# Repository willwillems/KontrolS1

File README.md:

The following info is all about the S4 MK1, the MK2 has a different (non-panelized) PCB design and thus doesn't allow for reusing the original PCB's without serious modifications. The MK3 also has a single PCB for the mixer and deck sections.

## Setup
- Use the `Kontrol_S1_LC_OLED` sketch
- Either `#include "unit_d.h"` or `#include "unit_c.h"` based on the unit
- Uncomment `#define SCREEN` if using the OLED module
- Edit the `MIDI_NAME` in the `name.c` file to the desired name (these cannot conflict with other S1 units you're using)
- Flash the firmware

## Led off states
All leds are controlled by a transistor activated by the 595 chip. However not all are connected the same way, sending 6 all-off byte packages (`0b00000000`) will turn some of the LED's on, these specific bits to be set to HIGH instead of LOW in order to be turned off.

```
// LED OFF STATES from least significant bit (so notation is in reverse)
// -- BYTE [0]: 0b01010101 --
// CUE1 green - CUE1 blue - CUE2 green - CUE2 blue - CUE3 green - CUE3 blue - CUE4 green - CUE4 blue 
// -- BYTE [1]: 0b00000000 --
// Sample 1 - Sample 2 - Sample 3 - Sample 4 - SYNC - CUE - PLAY - SHIFT
// -- BYTE [2]: 0b11000000 --
// ON AIR - SAMPLES - DECK A/B - DECK C/D - KEYLOCK - MASTER - TEMPO OFFSET UP - TEMPO OFFSET DOWN
// -- BYTE [3]: 0b00000000 --
// LOOP IN - LOOP OUT - TOGGLE DECK C/D - LOAD - NONE - NONE - NONE -NONE
// -- BYTE [4]: 0b11111111 -- LEFT DIGIT
// UP-MIDDLE - UP-RIGHT - DOT - UP-LEFT - DOWN-LEFT - DOWN-MIDDLE - MIDDLE-MIDDLE - DOWN-RIGHT
// -- BYTE [5]: 0b11111111 -- RIGHT DIGIT
// DM - DL - UL - UM - UR - DR - MM - DOT
```

## Button off states
The first four bits of the last packet are connected to GND trough some 330 R resistors. 

```
// BUTTON OFF STATES
// -- BYTE [0]: 0B00000000 --
// PLAY - CP4 - CUE - CP3 - SYNC - CP2 - SHIFT - CP1
// -- BYTE [1]: 0B00000000 --
// S4 - LOAD - S3 - LOOP OUT - S2 - LOOP IN - DECK C/D
// -- BYTE [2]: 0B00001100 --
// X - X - X - X - ENC-R BUT - ENC-L BUT - OFFSET DOWN - OFFSET UP
```

## Pinout
This is the pinout for the DECK A board the DECK B connector is almost identical (but mirrored). The two exceptions are pin 2 and 13, ~~I have no idea what pin 2 is~~ pin 2 is the 165's DS on the DECK B unit. Click [here](https://i.imgur.com/EdCKgI3.jpg) for the DECK B section.

> WARNING: Pinout changed, check below.

```
// 595’s output enable is connected to GND.
// 165’s CE (chip enable) is connected to GND.
// (13, 14, 15), (16, 17) and (18, 19) are connected together.

1. Q7 (serial out 165)
2. GND (DS from 165's on DECK B)
3. PL (latch pin 165)
4. CP (clock input 165)
5. ENC4-R (330 R)
6. ENC5-L (330 R)
7. ENC4-R (330 R)
8. ENC5-L (330 R)
9. Q7S (serial out 595) (for DECK B this is the serial out of the 4 upper 595's)
10. DS (serial in 595) (for DECK B this is the serial in of the 2 lower 595's)

11. ST_CP (latch pin 595)
12. SH_CP (clock input 595)
13. GND (For DECK B this is the serial in for the 4 upper 595's)
14. GND
15. GND
16. LED V1 (5v but can just be 3.v)
17. LED V1 (5v but can just be 3.v)
18. LED V2 (3.3v)
19. LED V2 (3.3v)
20. VCC

1. GND
2. VCC
3. POT
4. GND
```

## Chip connections

### 74HC595

There are 6 595 chips chained together (the serial out(`Q7S`) for the last 595 is exposed as pin 9 on the connector).

- `ST_CP` and `SH_CP` of every chip are connected to connector pin 11 and 12.
- `MR` is connected to `VCC` on every chip.
- Output enable (`OE`) is connected to `GND` on every chip.

### 74HC165

There are 3 165 chips chained together.

- Clock enable(`CE`) is connect to `GND` on every chip.
- `PL` and `CP` of every chip are connected to connector pin 3 and 4.

## Jog wheels

The rotation of the jogs is measured by two photo-interrupters ([KTIR0611S](http://www.farnell.com/datasheets/2307823.pdf)). The "push down" of the jog is measured by a photo sensor that gets blocked when you push the platter down on it.

### Connections
The 6 pin JST connector is connected to the circuit with the two photo-interrupters. There is also a connection to a third photo-interrupter but they did not end up mounting and integrating this third one into the final product.
```
1. VCC (3.3v)
2. VCC (3.3v) (this "enables" the optical readings?) 
3. GND
4. ENC R
5. ENC L
6. ENC M (not connected or mounted)
```
The 3 color push cable coming out of the jog:
```
BLUE. GND
RED. VCC (3.3V)
WHITE. SIGNAL (analog read: 800~900 off, 1023 on)
-. DUMMY (unused pin on 4-pin JST connector) 
```
> ## Warning
> The jog press is not yet working so the info about it is possibly wrong. The MK1 does seem to use a IR proximity sensor (probably the [HSDL-9100-024](https://docs.broadcom.com/doc/AV02-2259EN) but so far no reliable readings have been produced. The MK2 uses an Ambient Light Sensor with an I2C Interface called the [VNCL4000](https://cdn-shop.adafruit.com/datasheets/vcnl4000.pdf). The current MK1 problems might just be calibration issues but could also be something more serious.

## Observations
- VCC should be 3.3v, not 5v. The 595 works with 5v and you will not fry the LED's but the 165 will not work and you might damage it.
- You can easily run the 165 and 595 chips with hardware SPI.
- The left and right circuit board are not identical at all though the connectors appear to be.

## Custom FX PCB

The custom FX PCB has the same layout on both sides so only one version is required (it has both the L&R mounting holes). The custom FX PCB provides a 165 and 595 interface for the buttons and LED's respectively and a separate connector for the potentiometer signals.

### Pinout

```
1. INH (165-15) [Clock enable]
2. SER (165-10) [Serial data input]
3. QH (595-9) [Serial data output]
4. LATCH 165 (165-1) [Parallel load input]
5. RCK (595-12) [storage register clock input]
6. QH (165-9) [Serial out]
7. SER (595-14)[Serial data input]
8. CLOCK
9. GND
10. VCC

11. VCC
12. GND
13. FX_3
14. FX_2
15. FX_1
16. FX_DW
```

## Parts

These simplified BOM's are for the MK4 releases of the brain and pot boards.

### Brain board

These are the parts needed to populate 1 brain board, to convert one S4 to two S1 units you'd need these parts x2.

| Part                                   | Amount | Value |
| -------------------------------------- | ------ | ----- |
| Molex Picoblade (1.25mm) 10-pin        | 3      |       |
| Molex Picoblade (1.25mm) 8-pin         | 1      |       |
| Molex Picoblade (1.25mm) 6-pin         | 3      |       |
| Molex Picoblade (1.25mm) 4-pin         | 2      |       |
| M3 metal standoffs                     | 4      | 15mm  |
| M3 metal screws                        | 8      | 6mm   |
| USB-B socket                           | 1      |       |
| Teensy LC                              | 1      |       |
| Capacitor US 1206                      | 1      | 100nF |
| Resistor US 1206 (0805 compatible)     | 1      | 1M    |

The 1M resistor might need a higher value.

### Pot board

These are the parts needed to populate 1 brain board, to convert one S4 to two S1 units you'd need these parts x2. The standoffs needed are already included with the brain BOM.

| Part                                   | Amount | Value |
| -------------------------------------- | ------ | ----- |
| Molex Picoblade (1.25mm) 10-pin        | 1      |       |
| Molex Picoblade (1.25mm) 6-pin         | 1      |       |
| Resistor US 0805                       | 5      | 82    |
| Resistor US 0805                       | 8      | 10K   |
| 74HC595D                               | 1      |       |
| 74HC165D                               | 1      |       |
| Capacitor US 1206                      | 6      | 100nF |

The four capacitors for the potentiometers might need a lower value.

## Custom OLED PCB

Contains adapter from 1.25mm JST to OLED, a step-up to 12V and some passive components the OLED driver needs.

### Pinout

```
1. GND
2. CLOCK
3. GND
4. MOSI
5. SS-SCREEN
6. VCC
7. DC
8. RST
```

# Screen

The screen uses https://github.com/ErikMinekus/traktor-api-client to get data from traktor + a local server to send it to the teensy over serial.

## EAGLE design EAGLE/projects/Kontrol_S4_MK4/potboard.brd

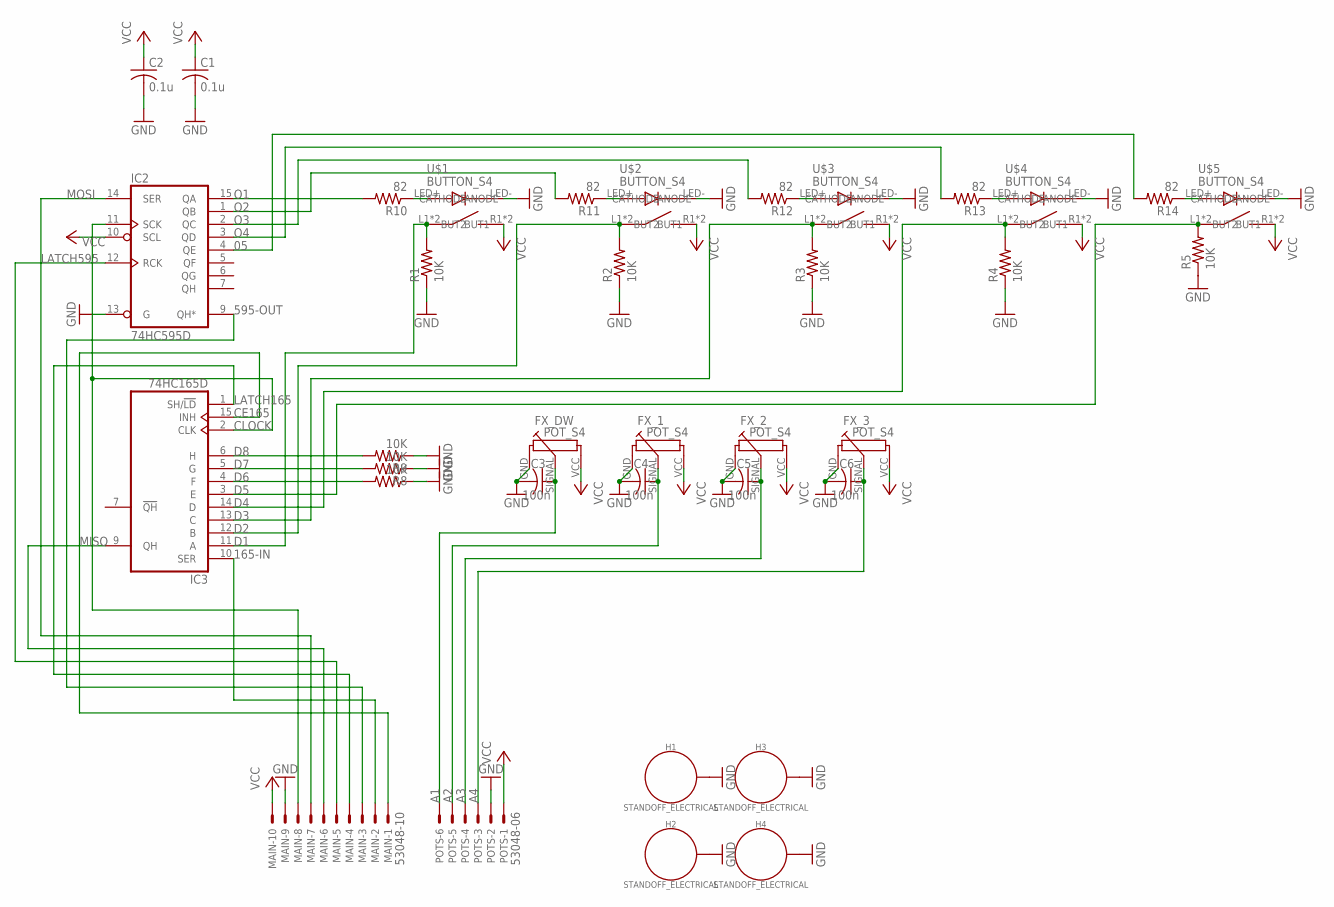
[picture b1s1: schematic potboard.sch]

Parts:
C1, C2: 0.1u; C1206
C3, C4, C5, C6: 100n; C1206
FX_1, FX_2, FX_3: POT_S4
FX_DW: POT_S4
H1, H2, H3, H4: STANDOFF_ELECTRICAL; STANDOFF-ELECTRICAL
IC2: 74HC595D; SO16
IC3: 74HC165D; SO16
MAIN: 53048-10
POTS: 53048-06
R1, R2, R3, R4, R5, R6, R8, R9: 10K; R0805
R10, R11, R12, R13, R14: 82; R0805
U$1, U$2, U$3, U$4, U$5: BUTTON_S4

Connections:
05: IC2.4 (QE), R14.2
165-IN: IC3.10 (SER), MAIN.2
595-OUT: IC2.9 (QH*), MAIN.3
A1: C3.1, FX_DW.SIGNAL (1S), POTS.6
A2: C4.1, FX_1.SIGNAL (1S), POTS.5
A3: C5.1, FX_2.SIGNAL (1S), POTS.4
A4: C6.1, FX_3.SIGNAL (1S), POTS.3
CE165: IC3.15 (INH), MAIN.1
CLOCK: IC2.11 (SCK), IC3.2 (CLK), MAIN.8
D1: IC3.11 (A), R1.2, U$1.L1 (BUT1), U$1.L2 (BUT1)
D2: IC3.12 (B), R2.2, U$2.L1 (BUT1), U$2.L2 (BUT1)
D3: IC3.13 (C), R3.2, U$3.L1 (BUT1), U$3.L2 (BUT1)
D4: IC3.14 (D), R4.2, U$4.L1 (BUT1), U$4.L2 (BUT1)
D5: IC3.3 (E), R5.2, U$5.L1 (BUT1), U$5.L2 (BUT1)
D6: IC3.4 (F), R6.2
D7: IC3.5 (G), R8.2
D8: IC3.6 (H), R9.2
GND: C1.2, C2.2, C3.2, C4.2, C5.2, C6.2, FX_1.GND (1A), FX_2.GND (1A), FX_3.GND (1A), FX_DW.GND (1A), H1.P1, H2.P1, H3.P1, H4.P1, IC2.8 (GND), IC2.13 (G), IC3.8 (GND), MAIN.9, POTS.2, R1.1, R2.1, R3.1, R4.1, R5.1, R6.1, R8.1, R9.1, U$1.LED- (CATHODE), U$2.LED- (CATHODE), U$3.LED- (CATHODE), U$4.LED- (CATHODE), U$5.LED- (CATHODE)
LATCH165: IC3.1 (SH/!LD), MAIN.4
LATCH595: IC2.12 (RCK), MAIN.5
MISO: IC3.9 (QH), MAIN.6
MOSI: IC2.14 (SER), MAIN.7
unnamed: R10.1, U$1.LED+ (ANODE)
unnamed: R11.1, U$2.LED+ (ANODE)
unnamed: R12.1, U$3.LED+ (ANODE)
unnamed: R13.1, U$4.LED+ (ANODE)
unnamed: R14.1, U$5.LED+ (ANODE)
O1: IC2.15 (QA), R10.2
O2: IC2.1 (QB), R11.2
O3: IC2.2 (QC), R12.2
O4: IC2.3 (QD), R13.2
VCC: C1.1, C2.1, FX_1.VCC (1E), FX_2.VCC (1E), FX_3.VCC (1E), FX_DW.VCC (1E), IC2.10 (SCL), IC2.16 (VCC), IC3.16 (VCC), MAIN.10, POTS.1, U$1.R1 (BUT2), U$1.R2 (BUT2), U$2.R1 (BUT2), U$2.R2 (BUT2), U$3.R1 (BUT2), U$3.R2 (BUT2), U$4.R1 (BUT2), U$4.R2 (BUT2), U$5.R1 (BUT2), U$5.R2 (BUT2)

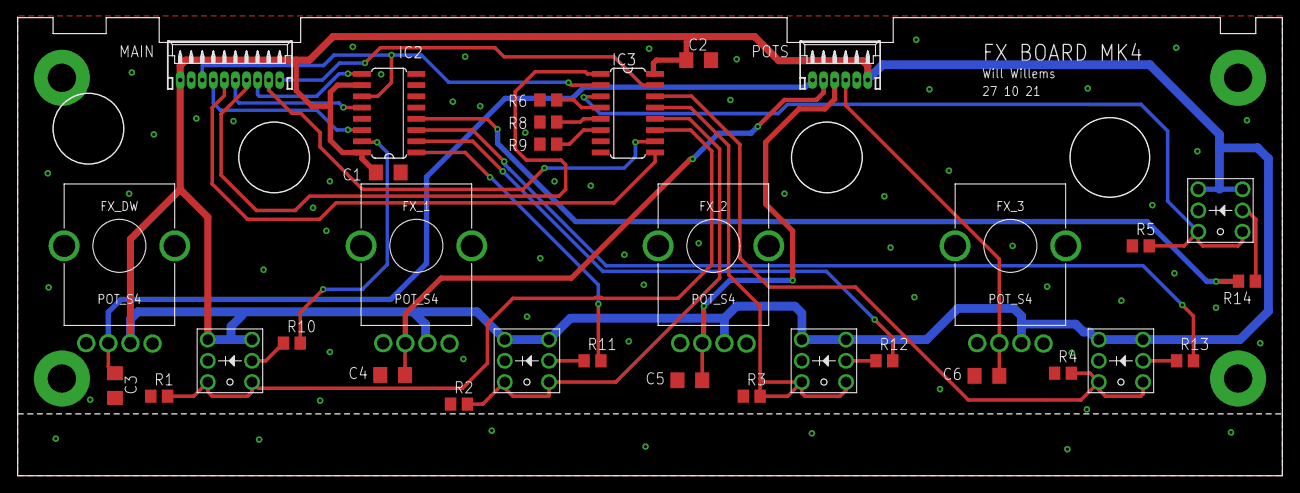
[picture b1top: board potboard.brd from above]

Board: 2 copper layers, 142.8 x 51.6 mm, 36 parts (0 on the bottom side), 32 nets.

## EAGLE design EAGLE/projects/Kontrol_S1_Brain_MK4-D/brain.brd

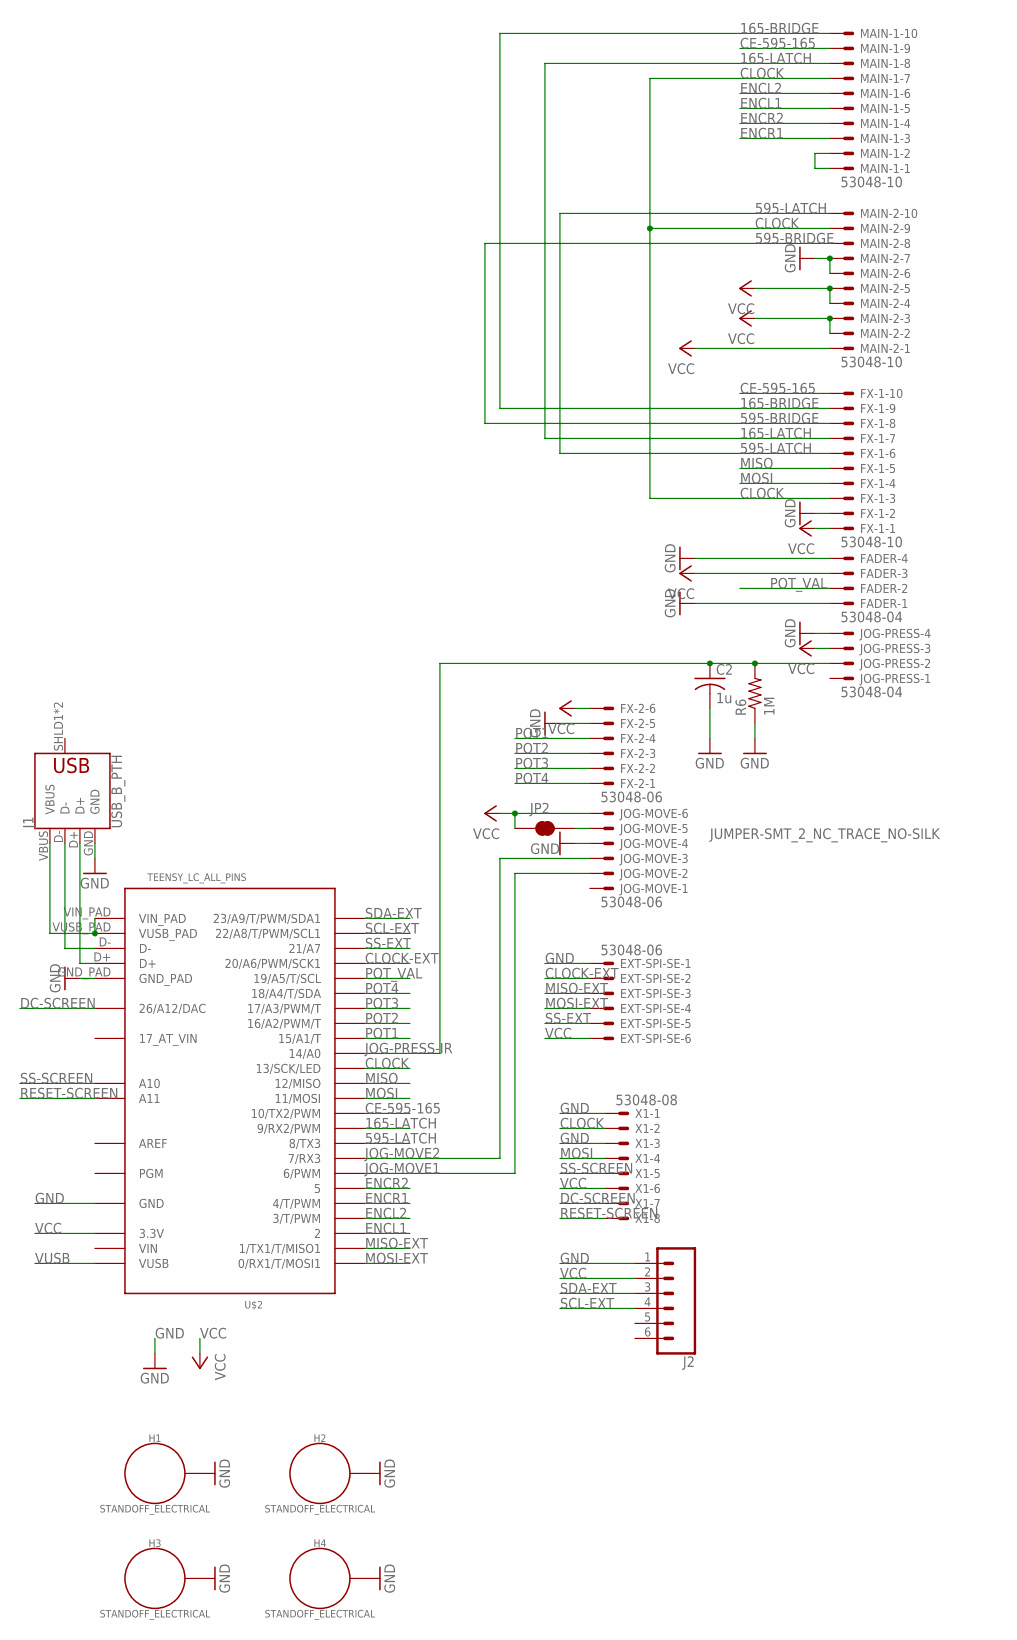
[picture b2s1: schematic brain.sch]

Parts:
C2: 1u; C1206
EXT-SPI-SE: 53048-06
FADER: 53048-04
FX-1: 53048-10
FX-2: 53048-06
H1, H2, H3, H4: STANDOFF_ELECTRICAL; STANDOFF-ELECTRICAL
J1: USB_B_PTH; USB-B-PTH
J2: CONN_06SILK_FEMALE_PTH; 1X06
JOG-MOVE: 53048-06
JOG-PRESS: 53048-04
JP2: JUMPER-SMT_2_NC_TRACE_NO-SILK; SMT-JUMPER_2_NC_TRACE_NO-SILK
MAIN-1, MAIN-2: 53048-10
R6: 1M; R1206
U$2: TEENSY_LC_ALL_PINS; TEENSY_3.0-3.2&LC_ALL_PINS
X1: 53048-08

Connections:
165-BRIDGE: FX-1.9, MAIN-1.10
165-LATCH: FX-1.7, MAIN-1.8, U$2.9 (9/RX2/PWM)
595-BRIDGE: FX-1.8, MAIN-2.8
595-LATCH: FX-1.6, MAIN-2.10, U$2.8 (8/TX3)
AREF: U$2.AREF
CE-595-165: FX-1.10, MAIN-1.9, U$2.10 (10/TX2/PWM)
CLOCK: FX-1.3, MAIN-1.7, MAIN-2.9, U$2.13 (13/SCK/LED), X1.2
CLOCK-EXT: EXT-SPI-SE.2, U$2.20/A6 (20/A6/PWM/SCK1)
DC-SCREEN: U$2.RESET/DAC (26/A12/DAC), X1.7
ENCL1: MAIN-1.5, U$2.2
ENCL2: MAIN-1.6, U$2.3 (3/T/PWM)
ENCR1: MAIN-1.3, U$2.4 (4/T/PWM)
ENCR2: MAIN-1.4, U$2.5
GND: C2.2, EXT-SPI-SE.1, FADER.1, FADER.4, FX-1.2, FX-2.5, H1.P1, H2.P1, H3.P1, H4.P1, J1.GND, J2.1, JOG-MOVE.4, JOG-PRESS.4, MAIN-2.6, MAIN-2.7, R6.1, U$2.AGND (GND), U$2.GND, U$2.GND1 (GND), U$2.GND_PAD, X1.1, X1.3
JOG-MOVE1: JOG-MOVE.2, U$2.6 (6/PWM)
JOG-MOVE2: JOG-MOVE.3, U$2.7 (7/RX3)
JOG-PRESS-IR: C2.1, JOG-PRESS.2, R6.2, U$2.14/A0
MISO: FX-1.5, U$2.12 (12/MISO)
MISO-EXT: EXT-SPI-SE.3, U$2.1 (1/TX1/T/MISO1)
MOSI: FX-1.4, U$2.11 (11/MOSI), X1.4
MOSI-EXT: EXT-SPI-SE.4, U$2.0 (0/RX1/T/MOSI1)
unnamed: JOG-MOVE.5, JP2.2
unnamed: MAIN-1.1, MAIN-1.2
unnamed: J1.VBUS, U$2.VIN_PAD, U$2.VUSB_PAD
unnamed: J1.D-, U$2.D-
unnamed: J1.D+, U$2.D+
POT1: FX-2.4, U$2.15/A1 (15/A1/T)
POT2: FX-2.3, U$2.16/A2 (16/A2/PWM/T)
POT3: FX-2.2, U$2.17/A3 (17/A3/PWM/T)
POT4: FX-2.1, U$2.18/A4 (18/A4/T/SDA)
POT_VAL: FADER.2, U$2.19/A5 (19/A5/T/SCL)
RESET-SCREEN: U$2.A11, X1.8
SCL-EXT: J2.4, U$2.22/A8 (22/A8/T/PWM/SCL1)
SDA-EXT: J2.3, U$2.23/A9 (23/A9/T/PWM/SDA1)
SS-EXT: EXT-SPI-SE.5, U$2.21/A7
SS-SCREEN: U$2.A10, X1.5
VCC: EXT-SPI-SE.6, FADER.3, FX-1.1, FX-2.6, J2.2, JOG-MOVE.6, JOG-PRESS.3, JP2.1, MAIN-2.1, MAIN-2.2, MAIN-2.3, MAIN-2.4, MAIN-2.5, U$2.3.3V, U$2.3.3V1 (3.3V), X1.6
VIN: U$2.VIN
VUSB: U$2.VUSB

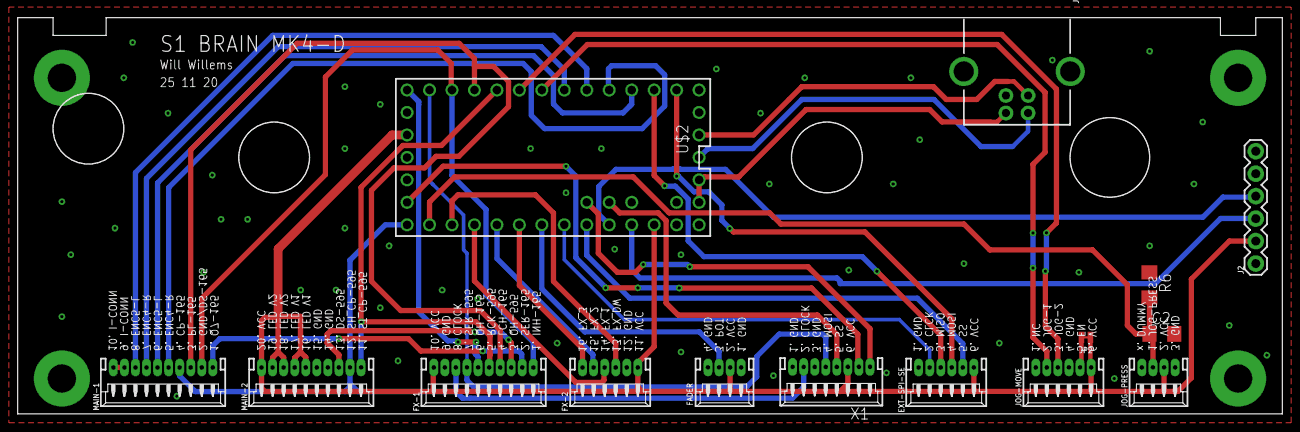
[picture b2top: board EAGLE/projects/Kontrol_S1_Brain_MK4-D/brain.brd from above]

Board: 2 copper layers, 142.8 x 44.6 mm, 19 parts (0 on the bottom side), 36 nets.

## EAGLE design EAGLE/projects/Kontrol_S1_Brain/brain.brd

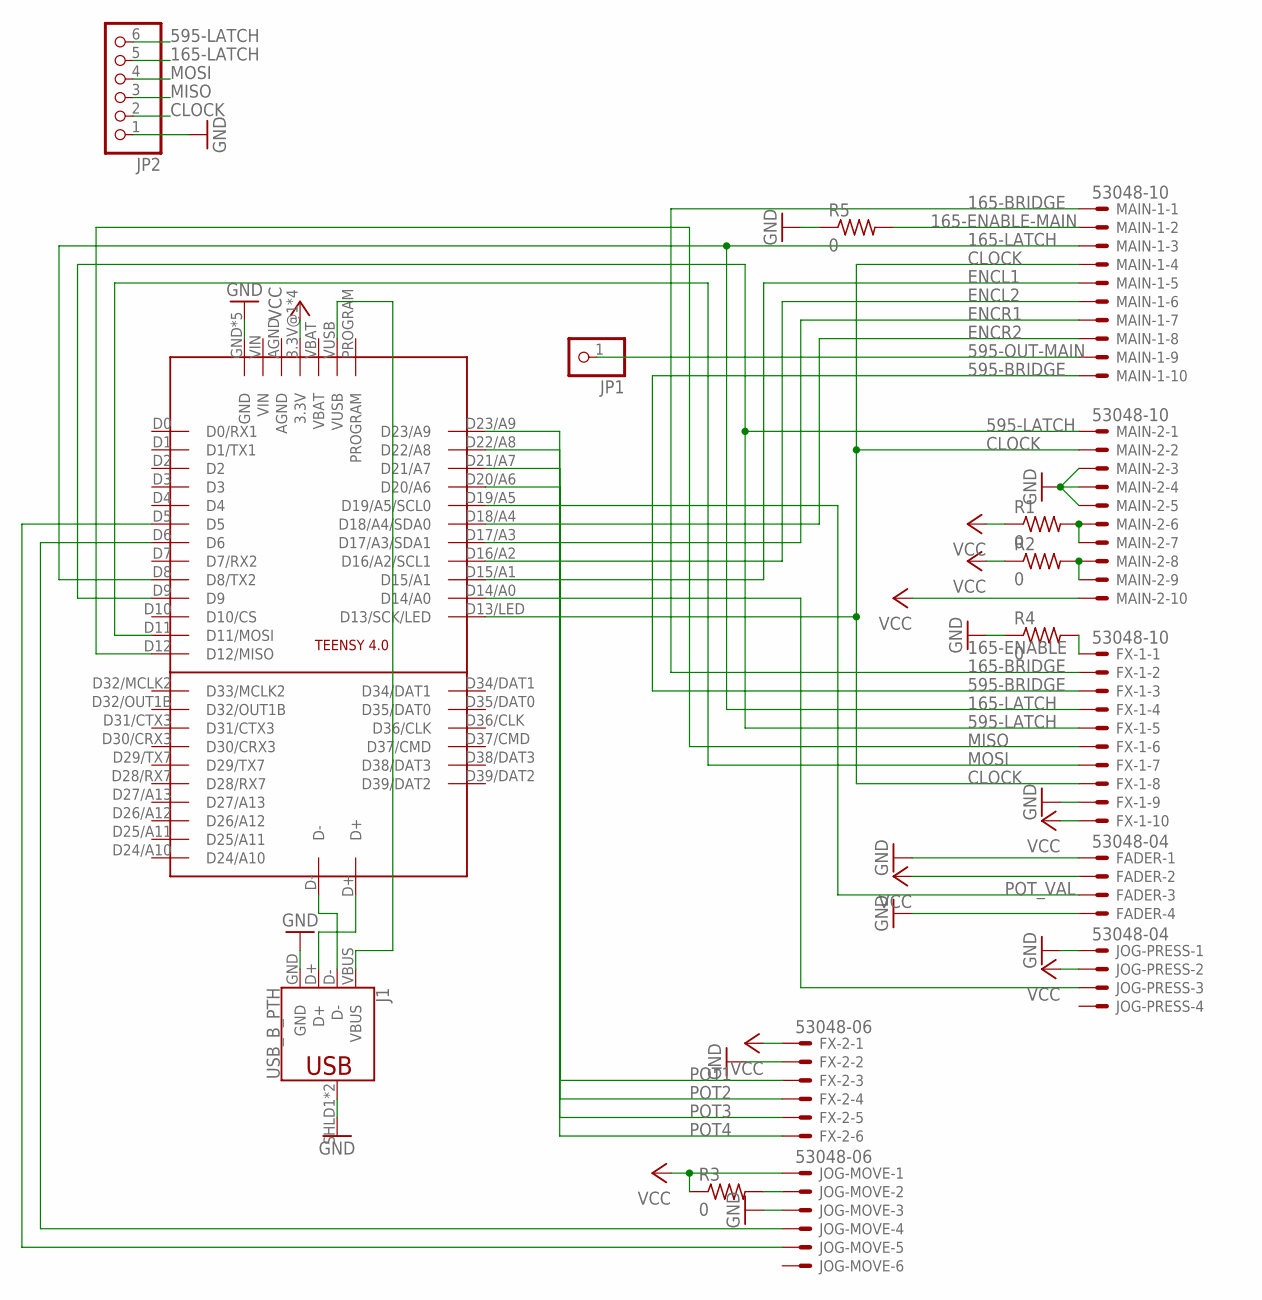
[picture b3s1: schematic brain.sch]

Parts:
FADER: 53048-04
FX-1: 53048-10
FX-2: 53048-06
J1: USB_B_PTH; USB-B-PTH
JOG-MOVE: 53048-06
JOG-PRESS: 53048-04
JP1: PINHD-1X1; 1X01
JP2: PINHD-1X6; 1X06
MAIN-1, MAIN-2: 53048-10
R1, R2, R3, R4, R5: 0; R1206
U$1: TEENSY-4.0-FULL-BRAKE-PADS

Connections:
165-BRIDGE: FX-1.2, MAIN-1.1
165-ENABLE: FX-1.1, R4.2
165-ENABLE-MAIN: MAIN-1.2, R5.2
165-LATCH: FX-1.4, JP2.5, MAIN-1.3, U$1.D8 (D8/TX2)
595-BRIDGE: FX-1.3, MAIN-1.10
595-LATCH: FX-1.5, JP2.6, MAIN-2.1, U$1.D9
595-OUT-MAIN: JP1.1, MAIN-1.9
CLOCK: FX-1.8, JP2.2, MAIN-1.4, MAIN-2.2, U$1.D13/LED (D13/SCK/LED)
ENCL1: MAIN-1.5, U$1.D15/A1
ENCL2: MAIN-1.6, U$1.D16/A2 (D16/A2/SCL1)
ENCR1: MAIN-1.7, U$1.D17/A3 (D17/A3/SDA1)
ENCR2: MAIN-1.8, U$1.D18/A4 (D18/A4/SDA0)
GND: FADER.1, FADER.4, FX-1.9, FX-2.2, J1.GND, J1.SHLD1 (SHIELD), J1.SHLD2 (SHIELD), JOG-MOVE.3, JOG-PRESS.1, JP2.1, MAIN-2.3, MAIN-2.4, MAIN-2.5, R4.1, R5.1, U$1.GND, U$1.GND@1 (GND), U$1.GND@2 (GND), U$1.P$11 (GND), U$1.P$12 (GND)
MISO: FX-1.6, JP2.3, U$1.D12 (D12/MISO)
MOSI: FX-1.7, JP2.4, U$1.D11 (D11/MOSI)
unnamed: MAIN-2.8, MAIN-2.9, R2.2
unnamed: MAIN-2.6, MAIN-2.7, R1.2
unnamed: JOG-PRESS.3, U$1.D14/A0
unnamed: JOG-MOVE.2, R3.2
unnamed: JOG-MOVE.4, U$1.D6
unnamed: JOG-MOVE.5, U$1.D5
unnamed: J1.D+, U$1.D+
unnamed: J1.D-, U$1.D-
unnamed: J1.VBUS, U$1.VUSB
POT1: FX-2.3, U$1.D20/A6
POT2: FX-2.4, U$1.D21/A7
POT3: FX-2.5, U$1.D22/A8
POT4: FX-2.6, U$1.D23/A9
POT_VAL: FADER.3, U$1.D19/A5 (D19/A5/SCL0)
VCC: FADER.2, FX-1.10, FX-2.1, JOG-MOVE.1, JOG-PRESS.2, MAIN-2.10, R1.1, R2.1, R3.1, U$1.3.3V@1 (3.3V), U$1.3.3V@2 (3.3V), U$1.3V3 (3.3V), U$1.ON/OFF (3.3V)

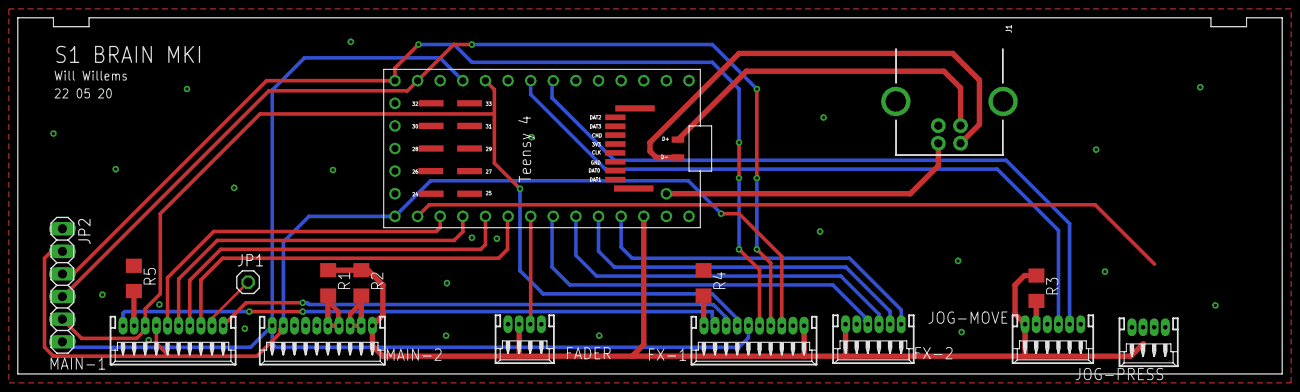
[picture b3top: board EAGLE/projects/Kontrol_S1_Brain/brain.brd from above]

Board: 2 copper layers, 142.0 x 40.0 mm, 16 parts (0 on the bottom side), 30 nets.

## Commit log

2020-01-24 working encoders, leds and display
2020-01-27 Add comments, write untested 165 read, fix vars
    - Add some comments to clarify functionality.
    - Fix some var names.
    - Add logging of 74HC165 input states on LED read, does not work yet.
2020-01-28 Create README
    Add chip info, pinout and default LED state.
2020-01-29 add jog section
2020-01-30 add working button reading
2020-01-30 Add jog pinouts, button packages/mapping & observations
2020-02-12 Add info about MK2 PCB
2020-02-12 add info about MK3 PCB
2020-05-08 Upload display demo
2020-05-09 Fully working demo
2020-05-09 Client for demo
2020-05-12 Add info about right DS pin to pinout
2020-05-12 Figure out jogs
2020-05-12 Fix potentiometer pinout
2020-05-12 Add pic from other PCB
2020-05-13 Change SPI speed, add jog & fader support
2020-05-13 Fix 165's not working
2020-05-16 Add early CAD files
2020-05-16 Add custom PCB pinout
2020-05-17 Add general description of FX PCB and about pinout
2020-05-19 Design logo
2020-05-19 Add header
2020-05-19 Fix logo alignment
2020-05-25 Add MK1 gerbers of boards to repo
2020-06-18 Add FX board integration, invert tempo & right encoder, fix 1 typo
2020-06-18 Add gerbers second revision FX board
2020-06-23 clean up project structure
2020-06-23 add info about 4 pin jog touch connector
2020-07-02 add warning posssible wrong info jog press working
2020-07-02 Update jog press warning
2020-09-22 add new gen board designs
2020-10-03 Add OLED PCB connections
2020-10-04 Add custom OLED board
2020-10-07 add note about 595 serial flow extra pin
2020-10-07 Substitute confusing left-right refrences for A-B
2020-10-17 add traktor mapping for S1-R
2020-10-17 add code for new brain
2020-10-19 update mapping
2020-10-19 Add draft of MK3 board
2020-10-19 extend ledmap for sample and range buttons
2020-10-25 D unit working, add buttonmap, multideck structure
2020-11-02 Add correct OLED driver pinout
2020-11-10 Quick screen update
2020-11-25 Add MK4 designs
2020-11-25 add FX board MK4
2020-11-25 add newest OLED LC sketch
2020-11-28 Fix small bugs add cue 5-8 fix loop-move bug
2020-11-28 add better debouncing and generalise
2020-12-09 Add simple BOM's
2020-12-09 add standoff length
2021-09-20 add screws to BOM
2021-10-27 fuck...
2021-10-27 update screw length
2021-10-27 remove outdated info
2021-10-27 update silkscreen
2021-10-31 update file
2021-10-31 update sketch
2022-10-16 c changes
2023-03-18 add 3d files for body smoothing
2023-03-18 start eagle conversion to KiCAD
2023-03-18 implement more reliable jog readings
2023-06-25 add info photo sensor
2023-07-04 add nect-gen KiCAD files
2023-07-09 add jog press schematic
2023-07-09 work

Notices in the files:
parts and their libraries:
SparkFun-Connectors: Licensing: Creative Commons ShareAlike 4.0 International - https://creativecommons.org/licenses/by-sa/4.0
